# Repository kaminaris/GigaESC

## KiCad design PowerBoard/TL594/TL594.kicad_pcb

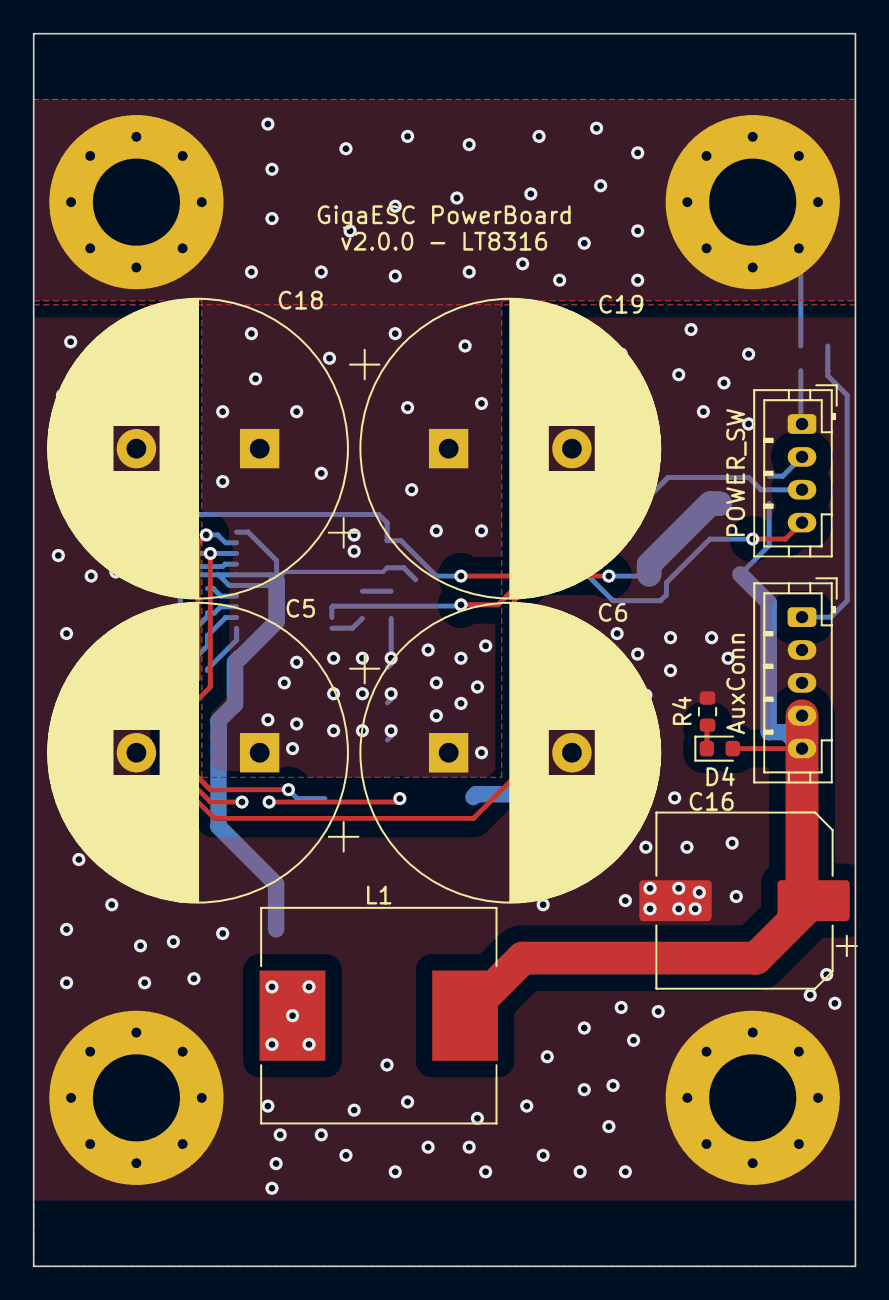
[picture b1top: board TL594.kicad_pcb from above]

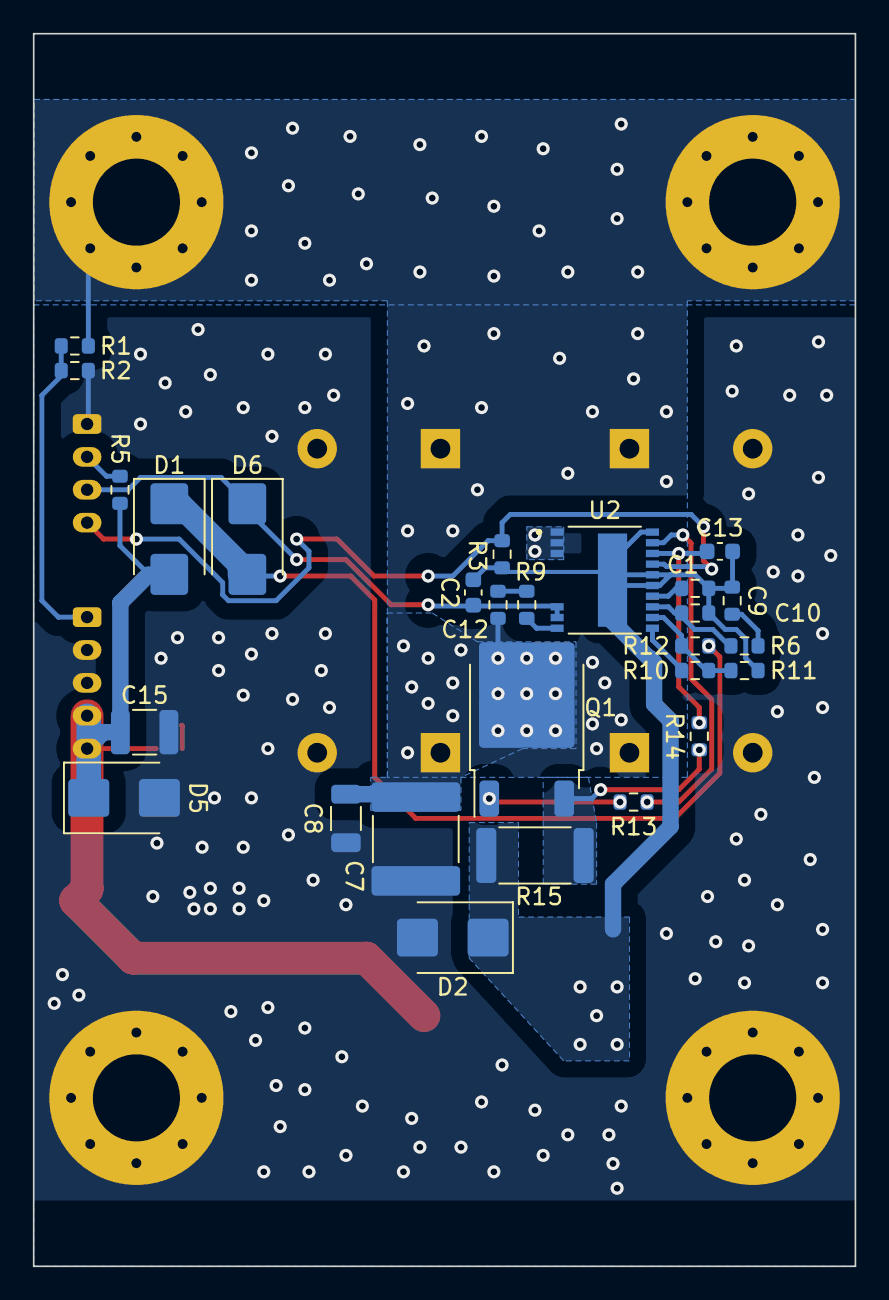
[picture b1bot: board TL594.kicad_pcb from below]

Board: 2 copper layers, 50.0 x 75.0 mm, 41 parts (27 on the bottom side), 21 nets.

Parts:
C1, C9: 100n; C_0603_1608Metric_L
C2: 10u; C_0603_1608Metric
C5, C6, C18, C19: 330u 200V; CP_Radial_D18.0mm_P7.50mm
C7: 1u 200V; C_2220_5650Metric
C8: 100n 200V; C_1206_3216Metric
C10, C12: 47p; C_0603_1608Metric_L
C13: 1n; C_0603_1608Metric
C15: 47u 16V; C_1210_3225Metric
C16: 470u 25V; CP_Elec_10x10.5
D1, D2, D6: SS520BF; D_SMB
D4: RUN; D_0603_1608Metric
D5: 3SMB5928B; D_SMB
H1, H2, H3, H4: MountingHole_Pad; MountingHole_5.3mm_M5_Pad_Via
J1: AuxConn; JST_PH_B5B-PH-K_1x05_P2.00mm_Vertical
J2: POWER_SW; JST_PH_B4B-PH-K_1x04_P2.00mm_Vertical
L1: 47uH; L_Chilisin_BMRG00131360
Q1: STD11N65M2; TO-252-2
R1: 150k; R_0603_1608Metric
R2: 2.7k; R_0603_1608Metric
R3, R5, R6, R9: 10k; R_0603_1608Metric
R4: 82k; R_0603_1608Metric
R10: 120k; R_0603_1608Metric
R11: 6.2k; R_0603_1608Metric
R12: 56k; R_0603_1608Metric
R13: 20; R_0603_1608Metric
R14: 100; R_0603_1608Metric
R15: 0.05; R_2512_6332Metric
U2: LT8316EFE#PBF; IC_LT8316EFE#PBF

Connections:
+12V: C15.1, C16.1, D1.2 (A), D4.2 (A), D5.1 (K), J1.4, J1.5, L1.2, R5.2
+BATT: C5.1, C6.1, C7.1, C8.1, C12.1, C18.1, C19.1, H2.1, H4.1, Q1.2 (D), R1.1, U2.1 (VIN), U2.2 (VIN), U2.3 (VIN)
-BATT: C5.2, C6.2, C7.2, C8.2, C15.2, C16.2, C18.2, C19.2, D2.2 (A), D5.2 (A), H1.1, H3.1, J1.2, J1.3, J2.1, R2.2, R4.1
GNDD: C1.2, C2.2, C9.2, C10.2, C13.2, D2.1 (K), L1.1, R3.2, R11.2, R15.1, U2.15 (GND), U2.16 (SMODE), U2.20 (GND), U2.21 (GND)
IN_V: J1.1, R1.2, R2.1
unnamed: C9.1, R6.2
unnamed: C12.2, R9.1
unnamed: D1.1 (K), D6.2 (A), R12.1
unnamed: D4.1 (K), R4.2
unnamed: C2.1, D6.1 (K), J2.3, U2.8 (INTVCC), U2.9 (BIAS)
unnamed: J2.2, R5.1
unnamed: J2.4, R3.1, U2.17 (EN/UVLO)
unnamed: Q1.1 (G), R13.2
unnamed: Q1.3 (S), R14.2, R15.2
unnamed: R9.2, U2.10 (DCM)
unnamed: R10.1, R11.1, R12.2, U2.12 (FB)
unnamed: R13.1, U2.19 (GATE)
unnamed: C1.1, U2.14 (IREG/SS)
unnamed: C13.1, R14.1, U2.18 (SENSE)
unnamed: R10.2, U2.11 (TC)
unnamed: C10.1, R6.1, U2.13 (VC)

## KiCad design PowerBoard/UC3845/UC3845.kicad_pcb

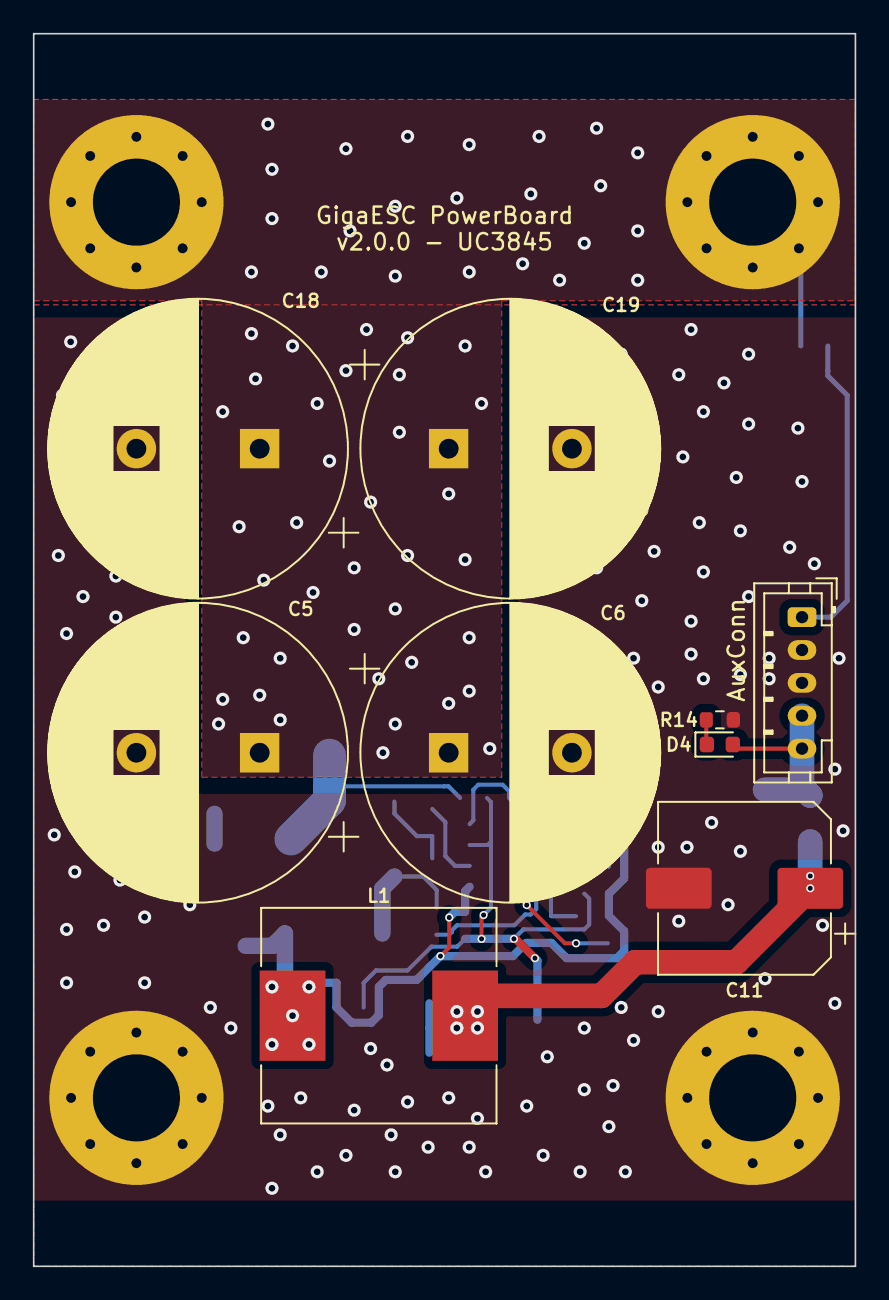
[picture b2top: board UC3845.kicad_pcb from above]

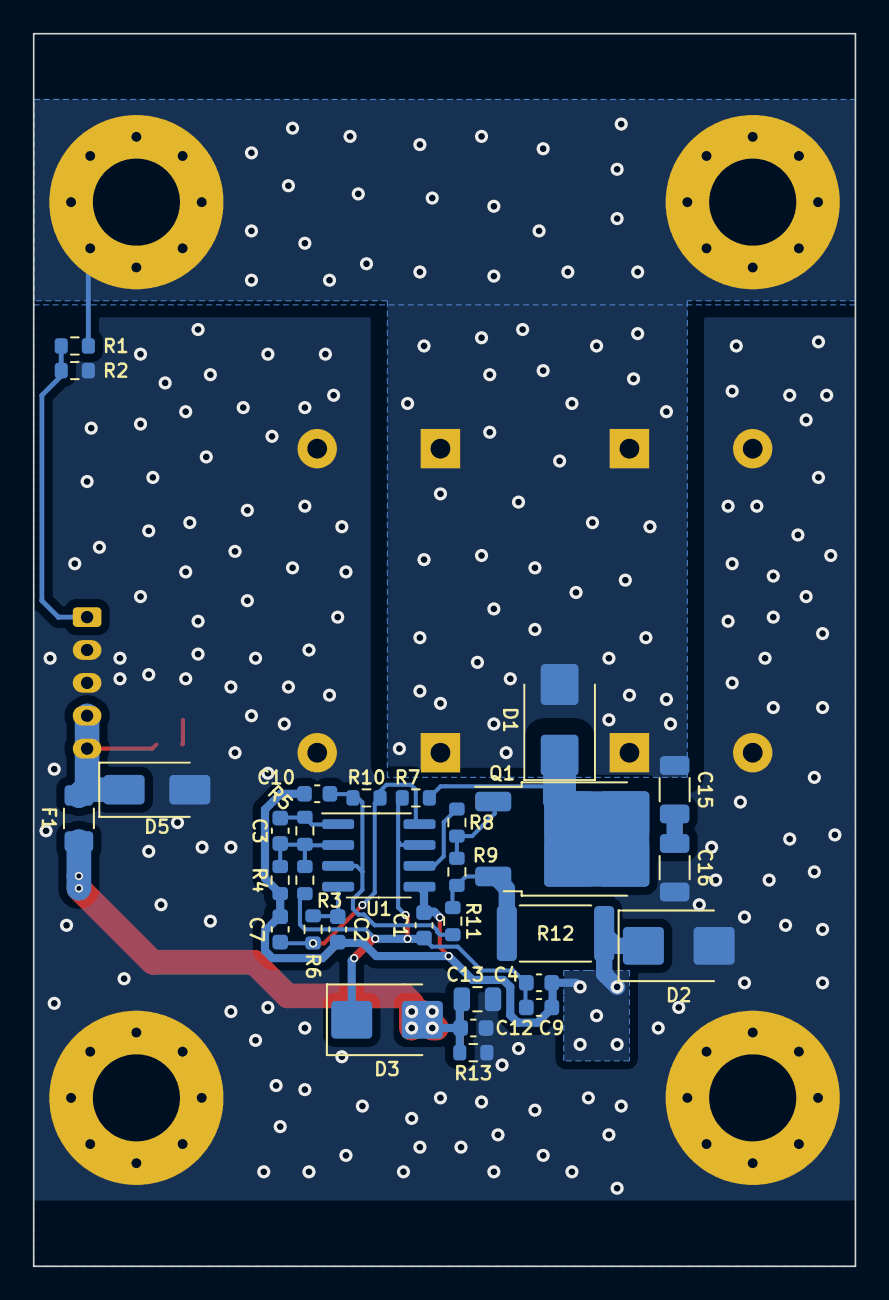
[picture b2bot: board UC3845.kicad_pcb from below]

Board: 2 copper layers, 50.0 x 75.0 mm, 44 parts (31 on the bottom side), 18 nets.

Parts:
C1, C4: 1u; C_0603_1608Metric
C2: 2.2n; C_0603_1608Metric
C3: 330p; C_0603_1608Metric
C5, C6, C18, C19: 330u 200V; CP_Radial_D18.0mm_P7.50mm
C7, C12: 100n; C_0603_1608Metric
C9: 10u 25V; C_0603_1608Metric
C10: 10n; C_0603_1608Metric
C11: 470u 35V; CP_Elec_10x10
C13: 2.2u; C_0805_2012Metric
C15, C16: 2.2u 100V; C_1206_3216Metric
D1, D2, D3: SS520BF; D_SMB
D4: RUN; D_0603_1608Metric
D5: 15V; D_SMA
F1: 3A; Fuse_1206_3216Metric
H1, H2, H3, H4: MountingHole_Pad; MountingHole_5.3mm_M5_Pad_Via
J1: AuxConn; JST_PH_B5B-PH-K_1x05_P2.00mm_Vertical
L1: 47uH; L_Chilisin_BMRG00131360
Q1: IRFR13N20DTRPBF; TO-252-2
R1: 150k; R_0603_1608Metric
R2: 2.7k; R_0603_1608Metric
R3, R14: 20k; R_0603_1608Metric
R4, R9: 5.1k; R_0603_1608Metric
R5: 200k; R_0603_1608Metric
R6, R10: 10k; R_0603_1608Metric
R7: 27k; R_0603_1608Metric
R8: 2.2; R_0603_1608Metric
R11: 1k; R_0603_1608Metric
R12: 50m; R_2512_6332Metric
R13: 390; R_0603_1608Metric
U1: UC3845BD1013TR; SOIC-8_3.9x4.9mm_P1.27mm

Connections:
+12V: D4.2 (A), D5.1 (K), F1.2, J1.4, J1.5
+BATT: C5.1, C6.1, C15.1, C18.1, C19.1, D1.2 (A), H2.1, H4.1, R1.1
-BATT: C5.2, C6.2, C11.2, C12.2, C13.2, C16.2, C18.2, C19.2, D2.2 (A), D5.2 (A), H1.1, H3.1, J1.2, J1.3, R2.2, R13.2, R14.1
GNDD: C1.2, C2.2, C4.2, C7.2, C9.2, C10.2, D2.1 (K), L1.1, R4.2, R12.2, U1.5 (GND)
IN_V: J1.1, R1.2, R2.1
unnamed: C15.2, C16.1
unnamed: D1.1 (K), Q1.2 (D), R7.1
unnamed: C11.1, C12.1, C13.1, D3.2 (A), F1.1, L1.2, R13.1
unnamed: C1.1, C4.1, C9.1, D3.1 (K), R3.2, R7.2, U1.7 (VCC)
unnamed: D4.1 (K), R14.2
unnamed: Q1.1 (G), R8.2, R9.1
unnamed: Q1.3 (S), R9.2, R11.2, R12.1
unnamed: C3.1, R5.2, U1.1 (COMP)
unnamed: C10.1, R10.2, R11.1, U1.3 (CS)
unnamed: C3.2, R3.1, R4.1, R5.1, U1.2 (FB)
unnamed: R8.1, U1.6 (OUT)
unnamed: C2.1, R6.2, U1.4 (RC)
VREF: C7.1, R6.1, R10.1, U1.8 (VREF)

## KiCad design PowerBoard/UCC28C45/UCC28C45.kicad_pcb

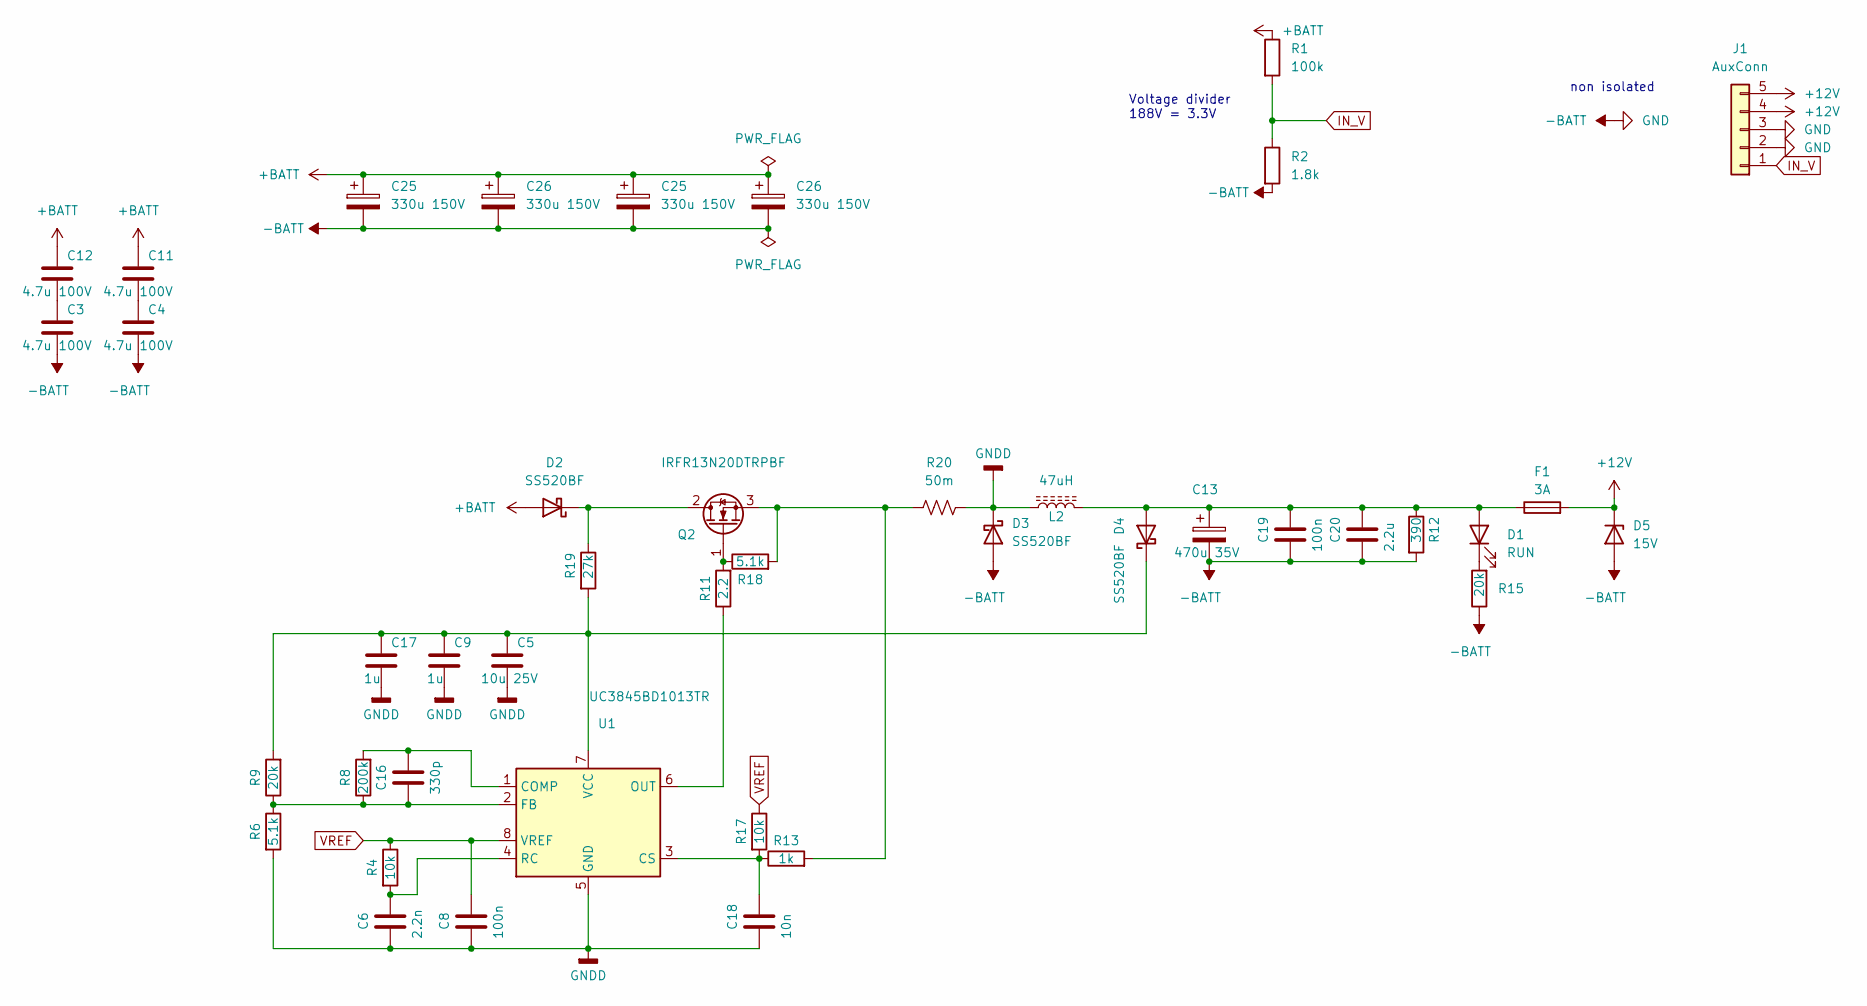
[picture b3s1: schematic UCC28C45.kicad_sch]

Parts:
C3, C4, C11, C12: 4.7u 100V; C_1206_3216Metric; MPN C237304; Mouser 81-GRM55DR72D105KW1L
C5: 10u 25V; C_0603_1608Metric_L; MPN C96446
C6: 2.2n; C_0603_1608Metric_L; Mouser 81-GRM55DR72D105KW1L
C8, C19: 100n; C_0603_1608Metric_L; MPN C14663; Mouser 81-GRM55DR72D105KW1L
C9, C17: 1u; C_0603_1608Metric_L; MPN C15849; Mouser 81-GRM55DR72D105KW1L
C13: 470u 35V; CP_Elec_10x10; MPN C72519
C16: 330p; C_0603_1608Metric_L; MPN C1664; Mouser 581-08055C104KAT4A
C18: 10n; C_0603_1608Metric_L; MPN C15849; Mouser 81-GRM55DR72D105KW1L
C20: 2.2u; C_0603_1608Metric_L; MPN C15849; Mouser 81-GRM55DR72D105KW1L
C25, C26: 330u 150V; CP_Radial_D16.0mm_P7.50mm; MPN C2761574; Mouser 661-EKMR201VS222MR50
D1: RUN; D_0603_1608Metric; MPN C2290
D2, D3, D4: SS520BF; D_SMB; MPN C123955
D5: 15V; D_SMA; MPN C110524
F1: 3A; Fuse_1206_3216Metric; MPN C2838915
J1: AuxConn; JST_XH_B5B-XH-A_1x05_P2.50mm_Vertical; MPN C157991
L2: 47uH; L_Chilisin_BMRG00131360; MPN C497913
Q2: IRFR13N20DTRPBF; TO-252-2; MPN C3021
R1: 100k; R_0603_1608Metric; MPN C25803; Mouser 603-RC0805FR-07100KL
R2: 1.8k; R_0603_1608Metric; MPN C4177; Mouser 71-CRCW0805-1.8K-E3
R4, R17: 10k; R_0603_1608Metric; MPN C25804; Mouser 603-AC0805JR-0710KL
R6, R18: 5.1k; R_0603_1608Metric; MPN C23186
R8: 200k; R_0603_1608Metric; MPN C25811
R9: 20k; R_0603_1608Metric; MPN C4184
R11: 2.2; R_0603_1608Metric; MPN C22939
R12: 390; R_0603_1608Metric; MPN C23151
R13: 1k; R_1206_3216Metric; MPN C4410
R15: 20k; R_0603_1608Metric; MPN C23254; Mouser 603-AC0805JR-0710KL
R19: 27k; R_0603_1608Metric; MPN C22967
R20: 50m; R_2512_6332Metric; MPN C2874774
U1: UC3845BD1013TR; SOIC-8_3.9x4.9mm_P1.27mm; MPN C7118; JLCRotOffset -270

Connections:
+12V: D5.1 (K), F1.2, J1.4, J1.5
+BATT: C11.1, C12.1, D2.2 (A), R1.1; also elsewhere on the board
-BATT: C3.2, C4.2, C13.2, C19.2, C20.2, D3.2 (A), D5.2 (A), J1.2, J1.3, R2.2, R12.2, R15.1; also elsewhere on the board
GNDD: C5.2, C6.2, C8.2, C9.2, C17.2, C18.2, D3.1 (K), L2.1, R6.2, R20.2, U1.5 (GND)
IN_V: J1.1, R1.2, R2.1
unnamed: C4.1, C11.2
unnamed: C3.1, C12.2
unnamed: C13.1, C19.1, C20.1, D1.2 (A), D4.2 (A), F1.1, L2.2, R12.1
unnamed: D1.1 (K), R15.2
unnamed: D2.1 (K), Q2.2 (D), R19.1
unnamed: C5.1, C9.1, C17.1, D4.1 (K), R9.2, R19.2, U1.7 (VCC)
unnamed: Q2.1 (G), R11.2, R18.1
unnamed: Q2.3 (S), R13.2, R18.2, R20.1
unnamed: C16.1, R8.2, U1.1 (COMP)
unnamed: C18.1, R13.1, R17.2, U1.3 (CS)
unnamed: C16.2, R6.1, R8.1, R9.1, U1.2 (FB)
unnamed: R11.1, U1.6 (OUT)
unnamed: C6.1, R4.2, U1.4 (RC)
VREF: C8.1, R4.1, R17.1, U1.8 (VREF)

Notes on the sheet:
non isolated
Voltage divider 188V = 3.3V

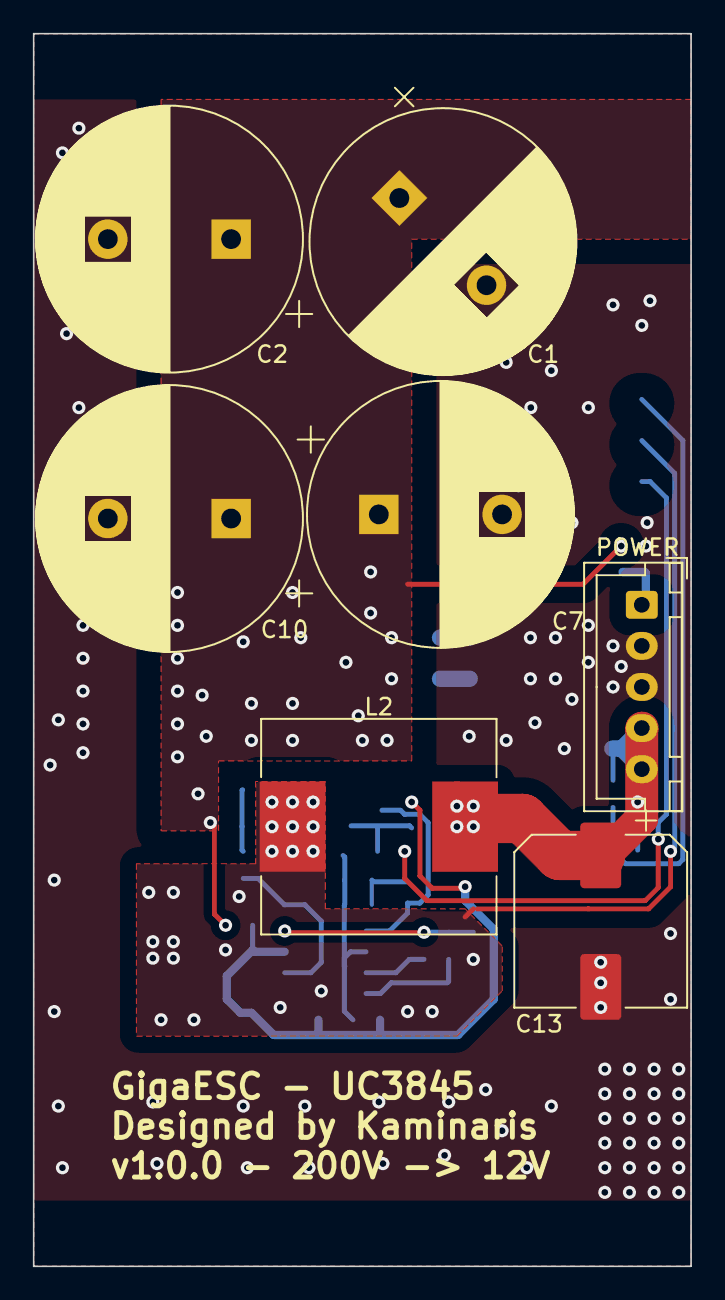
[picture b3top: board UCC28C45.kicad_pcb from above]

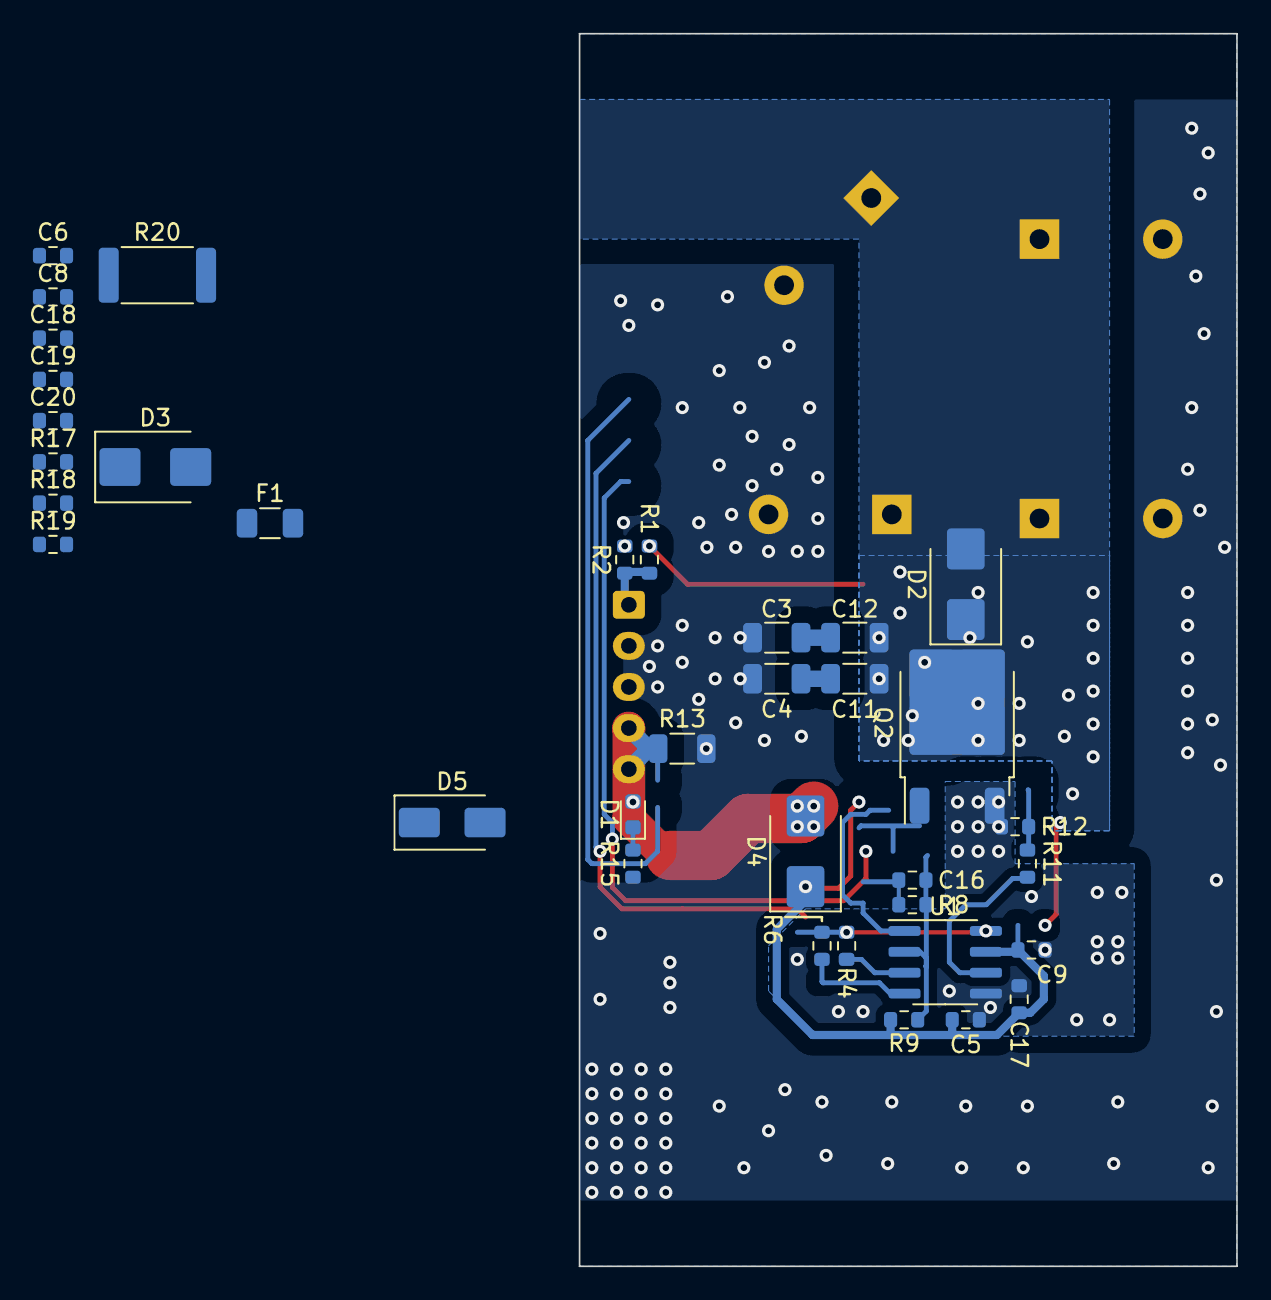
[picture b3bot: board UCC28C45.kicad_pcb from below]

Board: 2 copper layers, 40.0 x 75.0 mm, 42 parts (35 on the bottom side), 19 nets.

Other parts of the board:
C1, C2, C7, C10: 330u 150V; CP_Radial_D16.0mm_P7.50mm

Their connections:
+BATT: C1.1, C2.1, C7.1, C10.1; also elsewhere on the board
-BATT: C1.2, C2.2, C7.2, C10.2; also elsewhere on the board

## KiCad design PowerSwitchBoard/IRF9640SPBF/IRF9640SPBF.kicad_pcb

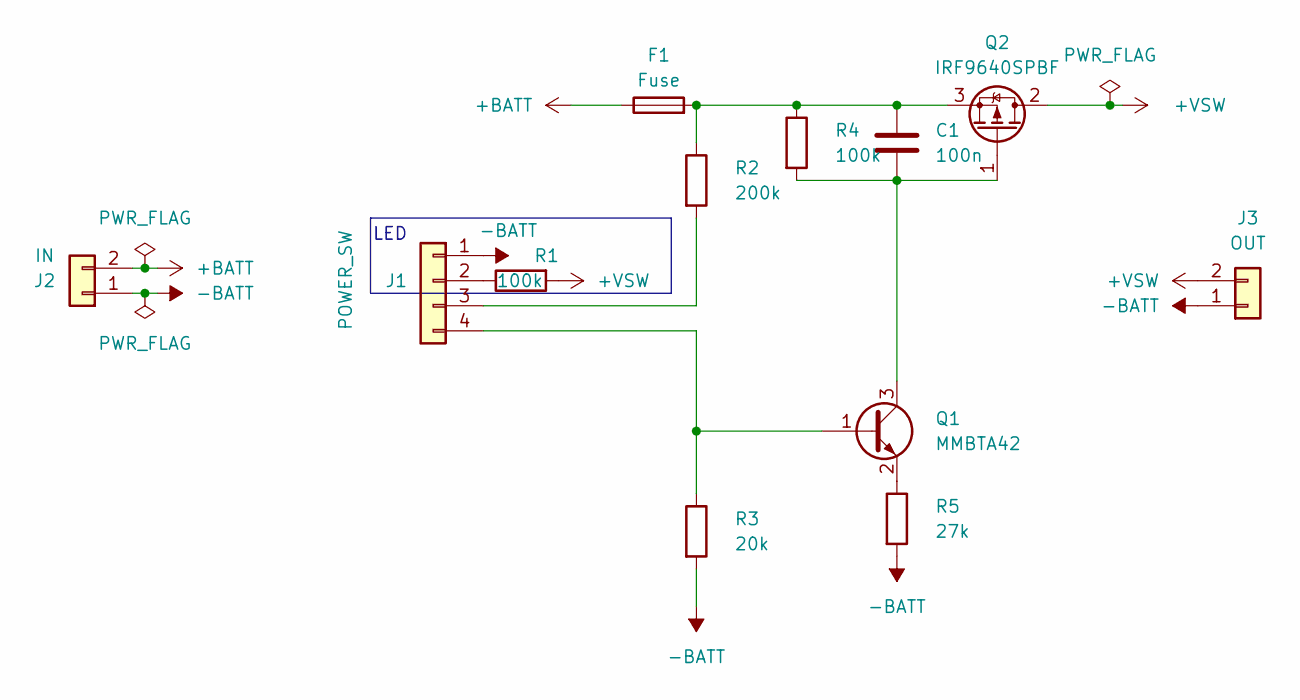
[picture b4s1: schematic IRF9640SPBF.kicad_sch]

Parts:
C1: 100n; C_0603_1608Metric; MPN C14663; Mouser 581-08055C104KAT4A
F1: Fuse; XuchengElecC3131; MPN C3131; JLCPosOffset 11.25,0
J1: POWER_SW; JST_PH_B4B-PH-K_1x04_P2.00mm_Vertical; MPN C131334; JLCRotOffset 180
J2: IN; AMASS_XT30PW-F_1x02_P2.50mm_Horizontal; MPN C2913282; JLCRotOffset 180
J3: OUT; AMASS_XT30PW-F_1x02_P2.50mm_Horizontal; MPN C2913282; JLCRotOffset 180
Q1: MMBTA42; SOT-23; MPN C916394; JLCRotOffset 180
Q2: IRF9640SPBF; TO-263-2; MPN C540971; JLCPosOffset -2,0
R1: 100k; R_0603_1608Metric; MPN C25803; Mouser 603-AC0805JR-0710KL
R2: 200k; R_0603_1608Metric; MPN C25811; Mouser 603-RC0805FR-0744K2L
R3: 20k; R_0603_1608Metric; MPN C4184; Mouser 603-RC0805FR-0744K2L
R4: 100k; R_0603_1608Metric; MPN C25803; Mouser 603-RC0805FR-0744K2L
R5: 27k; R_0603_1608Metric; MPN C22967; Mouser 603-RC0805FR-0744K2L

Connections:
+BATT: F1.1, J2.2
+VSW: J3.2, Q2.2 (D), R1.2
-BATT: J1.1, J2.1, J3.1, R3.2, R5.2
unnamed: J1.2, R1.1
unnamed: J1.3, R2.2
unnamed: J1.4, Q1.1 (B), R3.1
unnamed: C1.2, Q1.3 (C), Q2.1 (G), R4.2
unnamed: Q1.2 (E), R5.1
unnamed: C1.1, F1.2, Q2.3 (S), R2.1, R4.1

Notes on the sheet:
LED

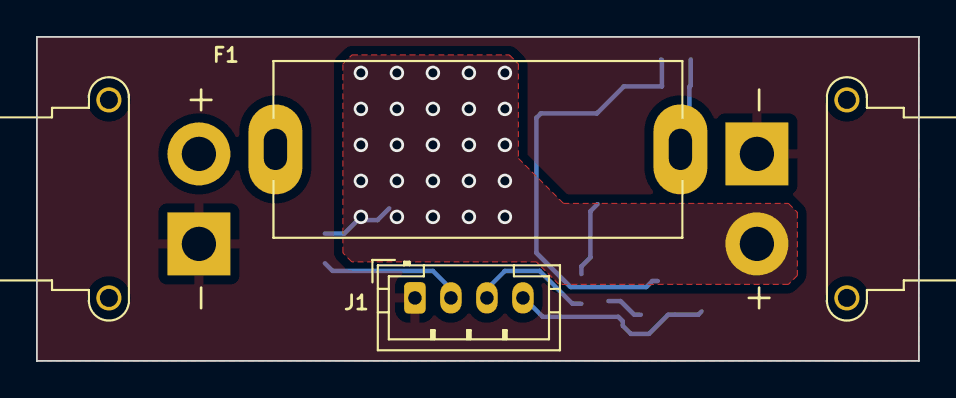
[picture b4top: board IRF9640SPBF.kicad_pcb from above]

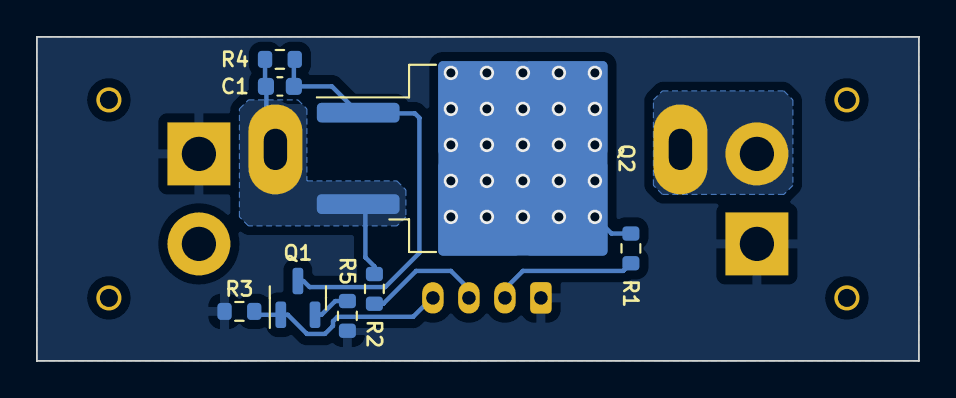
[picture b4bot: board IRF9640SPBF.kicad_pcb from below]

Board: 2 copper layers, 49.0 x 18.0 mm, 12 parts (8 on the bottom side), 9 nets.
